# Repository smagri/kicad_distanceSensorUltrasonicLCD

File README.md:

03jan2022

This  is a  KiCad schematic  and  PCB design  that was  produced as  a
project to learn KiCad.

It is a distance sensor using a HC-SR04 ultrasonic sensor and
displaying the the distance on a 1602LCD.  See images/ directroy, no
enclosure has yet been made.

PCB was manufactured by pcbway.com.

The PCB design could  do with a revison to pretty it up  and make it a
more sound design.

It was  originally produced to  be part  of the illabunda  eco village
Water Control System private project.  However, the design can be used
a general ultrasonic  sensor based as an  approximate distance measure
from 2cm - 400cm.  There are new plans for a PyDroid3 python based TCP
network RF version to be created now.

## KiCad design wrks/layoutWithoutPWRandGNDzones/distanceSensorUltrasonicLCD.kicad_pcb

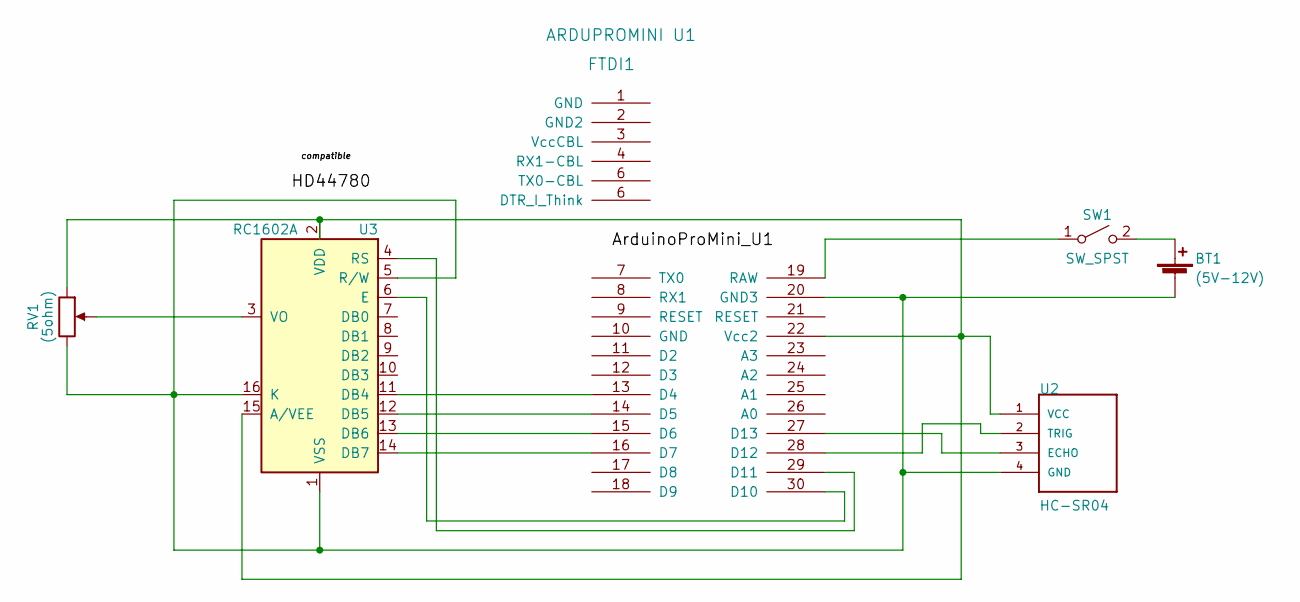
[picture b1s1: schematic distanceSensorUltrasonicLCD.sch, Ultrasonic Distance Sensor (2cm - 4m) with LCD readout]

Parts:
BT1: (5V-12V); BatteryHolder_Eagle_12BH611-GR
FTDI1: ARDUPROMINI U1; ArduProMini
RV1: (5ohm); Potentiometer_ACP_CA14V-15_Vertical
SW1: SW_SPST; PinSocket_1x02_P2.54mm_Vertical
U2: HC-SR04; XCVR_HC-SR04
U3: RC1602A; WC1602A

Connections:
unnamed: BT1.1 (+), SW1.2 (B)
unnamed: BT1.2 (-), FTDI1.20 (GND3), RV1.3, U2.4 (GND), U3.1 (VSS), U3.5 (R/W), U3.16 (K)
unnamed: FTDI1.13 (D4), U3.11 (DB4)
unnamed: FTDI1.14 (D5), U3.12 (DB5)
unnamed: FTDI1.15 (D6), U3.13 (DB6)
unnamed: FTDI1.16 (D7), U3.14 (DB7)
unnamed: FTDI1.19 (RAW), SW1.1 (A)
unnamed: FTDI1.22 (Vcc2), RV1.1, U2.1 (VCC), U3.2 (VDD), U3.15 (A/VEE)
unnamed: FTDI1.27 (D13), U2.3 (ECHO)
unnamed: FTDI1.28 (D12), U2.2 (TRIG)
unnamed: FTDI1.29 (D11), U3.4 (RS)
unnamed: FTDI1.30 (D10), U3.6 (E)
unnamed: RV1.2, U3.3 (VO)

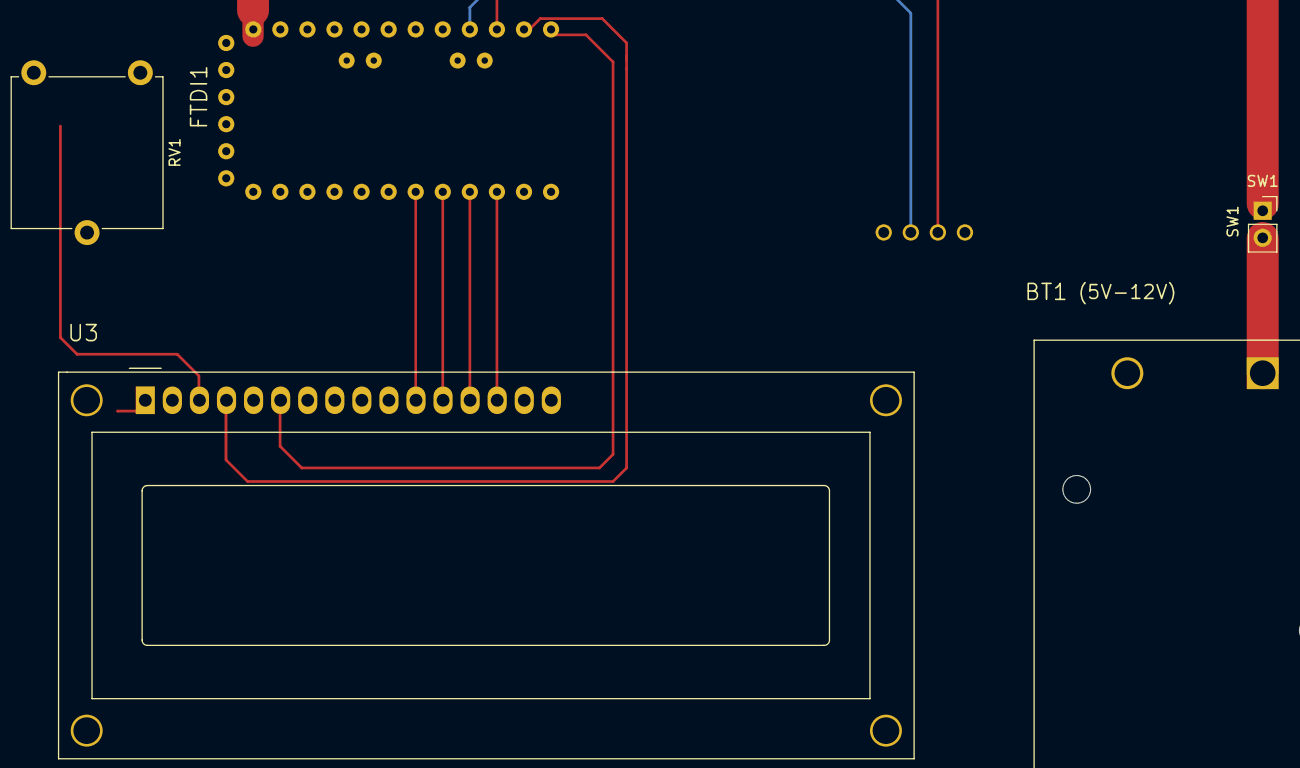
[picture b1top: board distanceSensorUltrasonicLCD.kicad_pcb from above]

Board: 2 copper layers, 6 parts (1 on the bottom side), 13 nets.

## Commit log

2022-01-02 adding readme file
2022-01-02 labelled .png pcb images
2022-01-02 Create LICENSE
